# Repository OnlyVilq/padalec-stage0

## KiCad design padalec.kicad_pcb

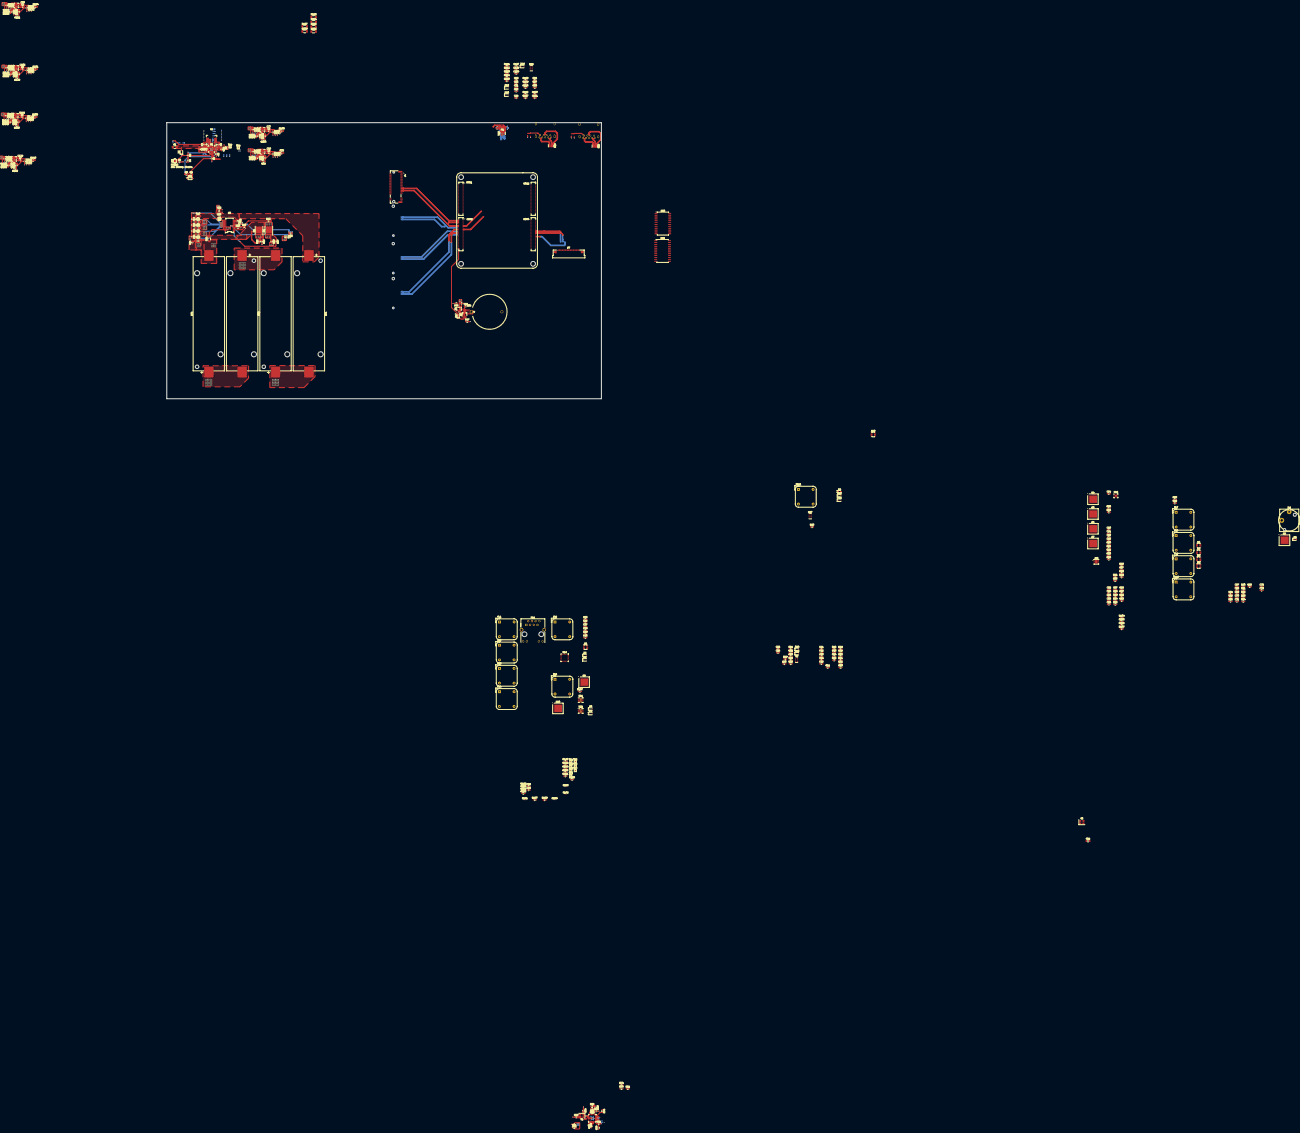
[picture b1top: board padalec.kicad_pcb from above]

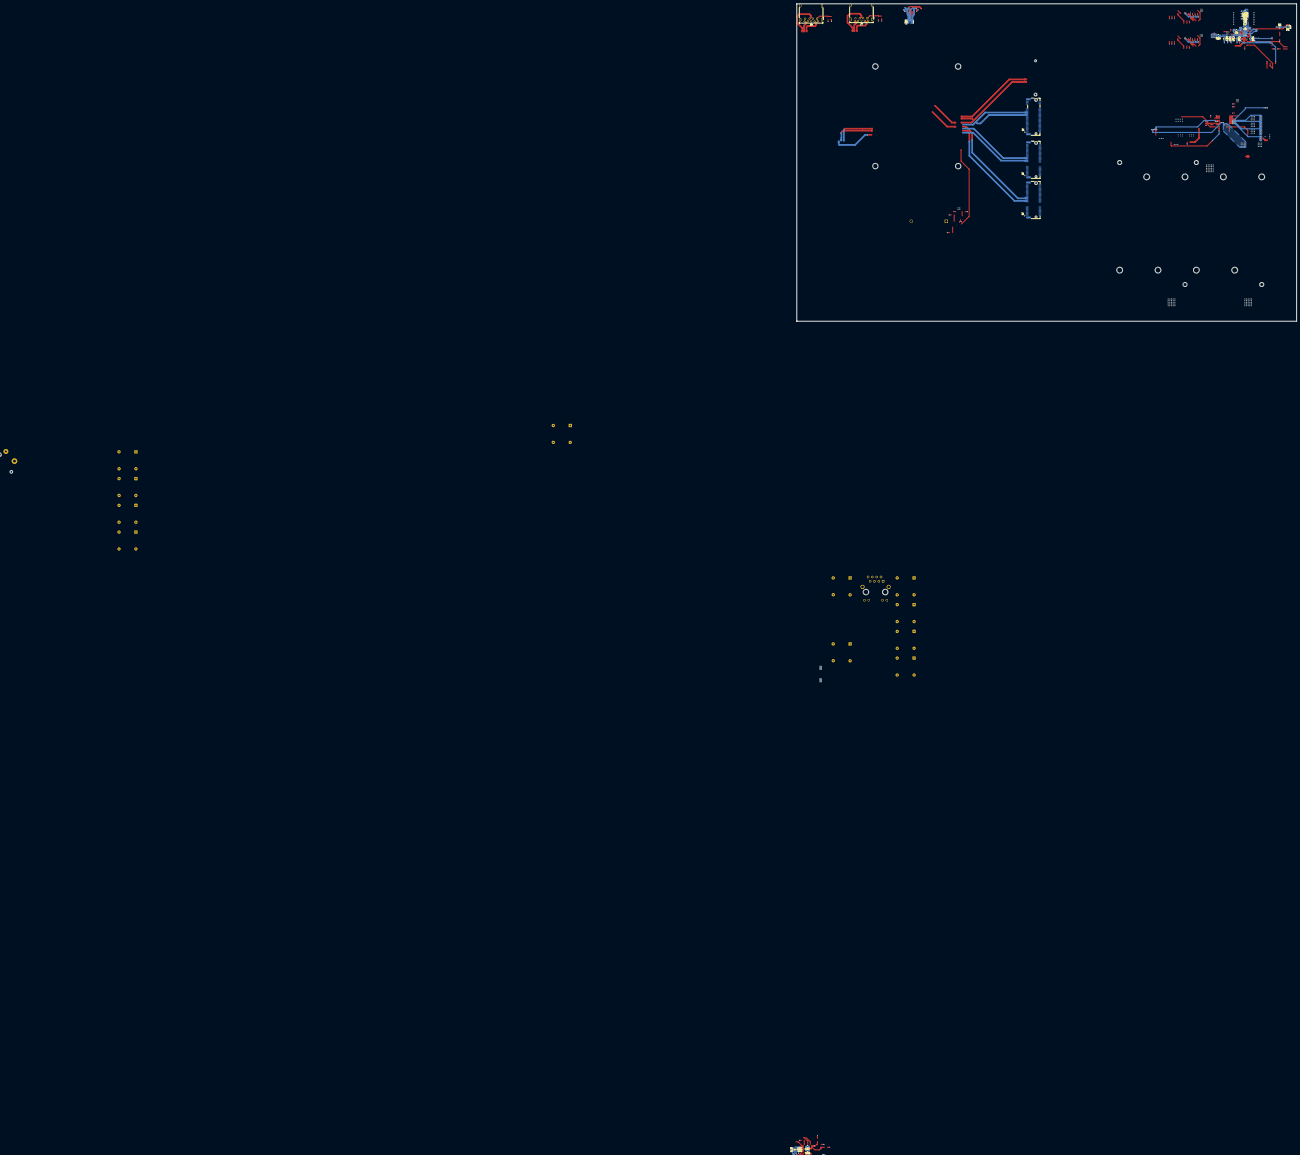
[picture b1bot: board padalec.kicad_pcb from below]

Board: 4 copper layers, 296.0 x 188.0 mm, 408 parts (26 on the bottom side), 299 nets.

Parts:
BT1, BT2, BT3, BT4: Battery_Cell; BatteryHolder_Keystone_1042_1x18650
BT5: Battery_Cell; BatteryHolder_MYOUNG_BS-07-A1BJ001_CR2032
C1, C2, C7, C8, C11, C13, C15, C22, C23, C25, C46, C47, C55, C65, C74, C75, C87, C91, C95, C96, C103, C104, C111, C112, C119, C120: 10u; C_0603_1608Metric_Pad1.08x0.95mm_HandSolder
C3, C6, C44, C45, C49, C53, C77, C81, C82, C85, C86, C88, C92, C98, C102, C106, C110, C114, C118, C122, C126: 0.1u; C_0603_1608Metric_Pad1.08x0.95mm_HandSolder
C4, C5: 47n; C_0603_1608Metric_Pad1.08x0.95mm_HandSolder
C9, C33: 1n; C_0603_1608Metric_Pad1.08x0.95mm_HandSolder
C10, C27, C28, C40, C42, C43: 4.7u; C_0603_1608Metric_Pad1.08x0.95mm_HandSolder
C12, C14, C17, C18, C19, C20, C21, C29, C54, C56, C64, C66, C128: 1u; C_0603_1608Metric_Pad1.08x0.95mm_HandSolder
C16, C26, C32, C34, C35, C36, C37, C41, C48, C57, C60, C61, C62, C63, C67, C70, C71, C72, C73, C76, C97, C105, C113, C121, C127, C129, C130, C131: 100n; C_0603_1608Metric_Pad1.08x0.95mm_HandSolder
C24: 10n; C_0603_1608Metric_Pad1.08x0.95mm_HandSolder
C30: 22n; C_0603_1608Metric_Pad1.08x0.95mm_HandSolder
C31: 2.2n; C_0603_1608Metric_Pad1.08x0.95mm_HandSolder
C38, C39: 6p; C_0603_1608Metric_Pad1.08x0.95mm_HandSolder
C50, C99, C107, C115, C123: 2.2u; C_0603_1608Metric_Pad1.08x0.95mm_HandSolder
C51, C52, C79, C80, C100, C101, C108, C109, C116, C117, C124, C125: 22u; C_0603_1608Metric_Pad1.08x0.95mm_HandSolder
C58, C59, C68, C69: 6.8p; C_0603_1608Metric_Pad1.08x0.95mm_HandSolder
C78: 3.3u; C_0603_1608Metric_Pad1.08x0.95mm_HandSolder
C83, C84: 220p; C_0603_1608Metric_Pad1.08x0.95mm_HandSolder
C89, C90, C93, C94: 150u; C_0603_1608Metric_Pad1.08x0.95mm_HandSolder
C132, C133: 33u; C_0603_1608Metric_Pad1.08x0.95mm_HandSolder
D1, D8, D9: LED; LED_0603_1608Metric_Pad1.05x0.95mm_HandSolder
D2, D3, D4, D5, D6, D10, D11, D12, D13, D14, D15, D16: PESD5V0X1BL; D_SOD-323
D7: eDP_30pin; Amphenol_F32Q-1A7x1-11029_1x29-1MP_P0.5mm_Horizontal
D17: BAT54; D_0603_1608Metric_Pad1.05x0.95mm_HandSolder
F1: Fuse; Fuse_1206_3216Metric_Pad1.42x1.75mm_HandSolder
FB1, FB2: BLM21A601R; L_0805_2012Metric_Pad1.05x1.20mm_HandSolder
FL1, FL2, FL3, FL4: Choke_Schaffner_RN102-04-14.0x14.0mm
FL5, FL6, FL7, FL8, FL9, FL10, FL11: DNP; Choke_Schaffner_RN102-04-14.0x14.0mm
J1: CM3588 Hirose Connector; CM3588
J4: Bus_M.2_Socket_M; AMPHENOL_MDT420M03001
J5: Bus_M.2_Socket_M; AMPHENOL_MDT420E03001
J6: Bus_M.2_Socket_E; AMPHENOL_MDT420M03001
J7, J8: USB3_A; USB3_A_Molex_48393-001
J9: Bus_M.2_Socket_E; AMPHENOL_MDT420E03001
J10: HDMI_A; WDFN-10-1EP_3x3mm_P0.5mm_EP1.8x2.5mm
J11: AudioJack3_SwitchTR; Jack_6.35mm_Neutrik_NJ2FD-V_Vertical
JP1: SCRAM; SolderJumper-2_P1.3mm_Open_RoundedPad1.0x1.5mm
L1: SPM6530T-1R0M120; SPM6530
L2, L4, L5, L6, L7: 2.2u; L_0603_1608Metric_Pad1.05x0.95mm_HandSolder
L3: 3.3u; L_0603_1608Metric_Pad1.05x0.95mm_HandSolder
P1: USB_C_Plug; USB_C_Plug_Molex_105444
Q1, Q2: CSD18534Q5A; VSONP-8-1EP_5x6_P1.27mm
Q3: AO3401A; TSOT-23_HandSoldering
Q4: AO3401A; Nordic_AQFN-94-1EP_7x7mm_P0.4mm
Q5: 2N7002; Nordic_AQFN-94-1EP_7x7mm_P0.4mm
Q6, Q7, Q8, Q9, Q10: NMOS; Nordic_AQFN-94-1EP_7x7mm_P0.4mm
R1, R5, R11, R13, R15, R16, R50, R59, R60, R61, R62, R66, R68, R71, R74, R75, R76, R77, R78, R79, R80, R81, R82, R84, R85, R86, R87, R88, R89, R90, R91, R92, R95, R96, R97, R99, R102, R116, R117, R118, R120, R123, R125, R127, R130, R132, R134, R137, R139, R141, R144, R155, R157, R158: 10k; R_0603_1608Metric_Pad0.98x0.95mm_HandSolder
R2, R7: 27k; R_0603_1608Metric_Pad0.98x0.95mm_HandSolder
R3, R54: 0; R_0603_1608Metric_Pad0.98x0.95mm_HandSolder
R4, R30, R36, R37, R38, R39, R40: DNP; R_0603_1608Metric_Pad0.98x0.95mm_HandSolder
R6, R154: 2.2k; R_0603_1608Metric_Pad0.98x0.95mm_HandSolder
R8: 5.24; R_0603_1608Metric_Pad0.98x0.95mm_HandSolder
R9: 30.31 k; R_0603_1608Metric_Pad0.98x0.95mm_HandSolder
R10, R29: 100; R_0603_1608Metric_Pad0.98x0.95mm_HandSolder
R12: 470k; R_0603_1608Metric_Pad0.98x0.95mm_HandSolder
R14, R27: 1k; R_0603_1608Metric_Pad0.98x0.95mm_HandSolder
R17, R46, R93, R94: 47k; R_0603_1608Metric_Pad0.98x0.95mm_HandSolder
R18, R72, R103, R124, R131, R138, R145: 0; R_0805_2012Metric_Pad1.20x1.40mm_HandSolder
R19, R20, R21, R22, R23: 68; R_1206_3216Metric_Pad1.30x1.75mm_HandSolder
R24: 1m; R_1206_3216Metric_Pad1.30x1.75mm_HandSolder
R25, R28, R57: 1M; R_0603_1608Metric_Pad0.98x0.95mm_HandSolder
R26: 4k5; R_0603_1608Metric_Pad0.98x0.95mm_HandSolder
R31, R32, R33, R34, R35, R41, R42, R43, R44: 33; R_0603_1608Metric_Pad0.98x0.95mm_HandSolder
R45, R48: R_Small; R_0603_1608Metric_Pad0.98x0.95mm_HandSolder
R47, R49, R58, R63, R64, R65, R67, R98, R106, R107, R109, R110, R111, R112, R114, R115, R119, R126, R133, R140, R156: 100k; R_0603_1608Metric_Pad0.98x0.95mm_HandSolder
R51: dnp; R_0603_1608Metric_Pad0.98x0.95mm_HandSolder
R52: 10; R_0603_1608Metric_Pad0.98x0.95mm_HandSolder
R53: 4.7k; R_0603_1608Metric_Pad0.98x0.95mm_HandSolder
R55: 10K; R_0603_1608Metric_Pad0.98x0.95mm_HandSolder
R56: 12K; R_0603_1608Metric_Pad0.98x0.95mm_HandSolder
R69, R100, R121, R128, R135, R142: 20k; R_0603_1608Metric_Pad0.98x0.95mm_HandSolder
R70, R122, R129, R136, R143: 45.3k; R_0603_1608Metric_Pad0.98x0.95mm_HandSolder
R73, R83: 1; R_0603_1608Metric_Pad0.98x0.95mm_HandSolder
R101: 73.2k; R_0603_1608Metric_Pad0.98x0.95mm_HandSolder
R104, R105: 2.2K; R_0603_1608Metric_Pad0.98x0.95mm_HandSolder
R108, R113: 37.4k; R_0603_1608Metric_Pad0.98x0.95mm_HandSolder
R146, R147, R148, R149, R150, R151, R152, R153: 499; R_0603_1608Metric_Pad0.98x0.95mm_HandSolder
R159, R160, R161, R162: 10k; R_0201_0603Metric_Pad0.64x0.40mm_HandSolder
R163, R164, R165, R166, R167, R168: 0; R_1206_3216Metric_Pad1.30x1.75mm_HandSolder
TH1, TH2: 103AT Thermistor; PinHeader_2x01_P1.00mm_Vertical_SMD
TP1: PowerEN; TestPoint_Pad_1.0x1.0mm
TP2: +5V; TestPoint_Pad_1.0x1.0mm
TP3: +3V3; TestPoint_Pad_1.0x1.0mm
TP4: 3V3_PCIE_A; TestPoint_Pad_1.0x1.0mm
TP5: 3V3_PCIE_B; TestPoint_Pad_1.0x1.0mm
TP6: 3V3 PCIE_C; TestPoint_Pad_1.0x1.0mm
TP7: 3V3 PCIE_D; TestPoint_Pad_1.0x1.0mm
TP8: VBUS; TestPoint_Pad_1.0x1.0mm
TP9: BAT; TestPoint_Pad_1.0x1.0mm
U1: BQ25798; Texas_RQM0029A_VQFN-29_4x4mm_P0.4mm
U2: BQ7791500PWR; BQ77915
U3, U17, U18, U19, U20, U27, U28: TPD6E05U06RVZ; Texas_R-PUSON-N14
U4: MCP73831-2-OT; SOT-23-5
U5: TPS22810DBV; SOT-23-6
U6: USB2534-1080AEN; SOT-23-6
U7, U8, U9, U10: 82400102; SOT-23-6
U11: TMJUTVW0021192448; RJ45_Hanrun_HR911105A_Horizontal
U12, U15, U23, U24, U25, U26: TPS56637; CONV_TPS56637RPAR
U13, U14: 9FGV0441; UQFN-32_5x5mm_P0.5mm
U16: FUSB302BMPX; WQFN-14-1EP_2.5x2.5mm_P0.5mm_EP1.45x1.45mm
U21, U22: TPS2561; VSON-10-1EP_3x3mm_P0.5mm_EP1.65x2.4mm_ThermalVias
U29, U30: PCA9539xD; SOIC-24W_7.5x15.4mm_P1.27mm
Y2, Y3: FC3BS; Crystal_SMD_3225-4Pin_3.2x2.5mm

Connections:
+1V8: FB1.1, FB2.1, R30.1, R154.1, R156.1
+3V3: C29.1, C130.1, C131.1, R7.1, R45.1, R54.1, R72.2, R104.1, R105.1, R159.1, R160.1, R161.1, R162.1, TP3.1 (1_1), U5.1 (VIN), U11.11, U16.3 (VDD), U16.4 (VDD), U30.24 (V_{DD})
+5V: C27.1, C87.1, C88.1, C91.1, C92.1, R103.2, R109.1, R110.1, R114.1, R115.1, TP2.1 (1_1), U4.4 (V_{DD}), U16.12 (VCONN), U16.13 (VCONN), U21.2 (IN), U21.3 (IN), U22.2 (IN), U22.3 (IN)
/Debug UART/RX: D6.2 (A2), R44.2, R45.2
/Debug UART/TX: D5.2 (A2), R43.2
/Debug UART/UART2_RX: J1.22, R44.1
/Debug UART/UART2_TX: J1.20, R43.1
/EDP 1/Bl_VCC: C30.2, D7.26 (Bl_VCC), D7.27 (Bl_VCC), D7.28 (Bl_VCC), D7.29 (Bl_VCC), R50.2
/EDP 1/LCD_VCC: C32.1, D7.12 (LCD_VCC), D7.13 (LCD_VCC), R51.2, R52.1, U5.6 (VOUT)
/EDP 1/eDP.AUX_N: D7.10 (AUX_N), J1.359
/EDP 1/eDP.AUX_P: D7.9 (AUX_P), J1.357
/EDP 1/eDP.Bl_PWR_EN: R48.1, U30.11 (IO0_7)
/EDP 1/eDP.Logic_EN: U5.3 (EN/UVLO), U30.10 (IO0_6)
/EDP 1/eDP.TX0_N: D7.6 (TX0_N), J1.347
/EDP 1/eDP.TX0_P: D7.7 (TX0_P), J1.345
/EDP 1/eDP.TX1_N: D7.3 (TX1_N), J1.341
/EDP 1/eDP.TX1_P: D7.4 (TX1_P), J1.339
/Ethernet/Gled: C44.1, J1.72, U11.12
/Ethernet/TD1_N: J1.80, U7.3
/Ethernet/TD1_P: J1.78, U7.1
/Ethernet/TD2_N: J1.86, U8.3
/Ethernet/TD2_P: J1.84, U8.1
/Ethernet/TD3_N: J1.92, U9.3
/Ethernet/TD3_P: J1.90, U9.1
/Ethernet/TD4_N: J1.98, U10.3
/Ethernet/TD4_P: J1.96, U10.1
/Ethernet/U10_4: FL1.3, U7.4
/Ethernet/U10_6: FL1.1, U7.6
/Ethernet/U11_4: FL2.3, FL3.3, U8.4
/Ethernet/U11_6: FL2.1, FL3.1, U8.6
/Ethernet/U12_4: FL4.3, U9.4
/Ethernet/U12_6: FL4.1, U9.6
/Ethernet/Yled: C45.1, J1.74
/GPIO expander/PCIEP.3V3_A: R163.1, U30.13 (IO1_0)
/GPIO expander/PCIEP.3V3_B: R164.1, U30.14 (IO1_1)
/GPIO expander/PCIEP.3V3_C: R165.1, U30.15 (IO1_2)
/GPIO expander/PCIEP.3V3_D: R166.1, U30.16 (IO1_3)
/GPIO expander/PCIEP.pGood_A: R119.2, U23.4 (PG), U30.17 (IO1_4)
/GPIO expander/PCIEP.pGood_B: R126.2, U24.4 (PG), U30.18 (IO1_5)
/GPIO expander/PCIEP.pGood_C: R133.2, U25.4 (PG), U30.19 (IO1_6)
/GPIO expander/PCIEP.pGood_D: R140.2, U26.4 (PG), U30.20 (IO1_7)
/GPIO expander/PCIe.~Disable1: J6.56 (~W_DISABLE1), R95.2, U29.4 (IO0_0)
/GPIO expander/PCIe.~Disable2: J6.54 (~W_DISABLE2), R96.2, U29.5 (IO0_1)
/GPIO expander/PCIe.~Disable3: J9.56 (~W_DISABLE1), R116.2, U29.6 (IO0_2)
/GPIO expander/PCIe.~Disable4: J9.54 (~W_DISABLE2), R117.2, U29.7 (IO0_3)
/GPIO expander/USB.EN1: J1.239, R106.1, U21.4 (EN1)
/GPIO expander/USB.EN2: J1.261, R111.1, U22.4 (EN1)
/GPIO expander/USB.EN3: J1.397, R112.1, U22.5 (EN2)
/GPIO expander/USB.~Fault1: R109.2, U21.10 (~FAULT1), U30.5 (IO0_1)
/GPIO expander/USB.~Fault2: R114.2, U22.10 (~FAULT1), U30.6 (IO0_2)
/GPIO expander/USB.~Fault3: R115.2, U22.6 (~FAULT2), U30.7 (IO0_3)
/GPIO expander/expander.SCL: J1.32, R160.2, U30.23 (SDA)
/GPIO expander/expander.SDA: J1.31, R159.2, U30.22 (SCL)
/GPIO expander/expander.~INT: J1.398, R161.2, U30.1 (~INT)
/GPIO expander/~RESET: R162.2, U30.3 (~RESET)
/HDMI_tx/D0+: FL10.2, J10.7 (D0+), U27.9 (D3+)
/HDMI_tx/D0-: FL10.4, J10.9 (D0-), U27.8 (D3-)
/HDMI_tx/D1+: FL9.2, J10.4 (D1+), U27.12 (D2+)
/HDMI_tx/D1-: FL9.4, J10.6 (D1-), U27.11 (D2-)
/HDMI_tx/D2+: FL8.2, J10.1 (D2+), U27.14 (D1+)
/HDMI_tx/D2-: FL8.4, J10.3 (D2-), U27.13 (D1-)
/HDMI_tx/HDMI.D0_N: FL10.3, R148.1
/HDMI_tx/HDMI.D0_P: FL10.1, R149.1
/HDMI_tx/HDMI.D1_N: FL9.3, R150.1
/HDMI_tx/HDMI.D1_P: FL9.1, R151.1
/HDMI_tx/HDMI.D2_N: FL8.3, R152.1
/HDMI_tx/HDMI.D2_P: FL8.1, R153.1
/HDMI_tx/HDMI.D3_N: FL11.3, R146.1
/HDMI_tx/HDMI.D3_P: FL11.1, R147.1
/Jack_35/DET: R156.2, R157.1
/Jack_35/HPL: C127.1, D16.2 (A2), J1.104, J11.T, R155.1
/Jack_35/HPR: C129.1, D15.2 (A2), J1.103, R158.1
/Jack_35/HP_DET: J1.108, R154.2
/PCIE/M2_E_x1/3v3: J6.2 (3.3V), J6.4 (3.3V), J6.72 (3.3V), J6.74 (3.3V), R95.1, R96.1, R138.2, TP6.1 (1_1)
/PCIE/M2_E_x2/3v3: J9.2 (3.3V), J9.4 (3.3V), J9.72 (3.3V), J9.74 (3.3V), R116.1, R117.1, R145.2, TP7.1 (1_1)
/PCIE/M2_M_x1/3v3: J4.2 (3.3V), J4.4 (3.3V), J4.12 (3.3V), J4.14 (3.3V), J4.16 (3.3V), J4.18 (3.3V), J4.70 (3.3V), J4.72 (3.3V), J4.74 (3.3V), R93.1, R124.2, TP4.1 (1_1)
/PCIE/M2_M_x2/3v3: J5.2 (3.3V), J5.4 (3.3V), J5.12 (3.3V), J5.14 (3.3V), J5.16 (3.3V), J5.18 (3.3V), J5.70 (3.3V), J5.72 (3.3V), J5.74 (3.3V), R94.1, R131.2, TP5.1 (1_1)
/PCIE/PCIE CLOCK 0/CK_REF_FG: R75.2, R81.1
/PCIE/PCIE CLOCK 0/FG_OE_0: R77.2, U13.12 (~OE0)
/PCIE/PCIE CLOCK 0/FG_OE_1: R78.2, U13.17 (~OE1)
/PCIE/PCIE CLOCK 0/FG_OE_2: R79.2, U13.24 (~OE2)
/PCIE/PCIE CLOCK 0/FG_OE_3: R80.2, U13.29 (~OE3)
/PCIE/PCIE CLOCK 0/FG_SSEN: R76.2, R82.1, U13.32 (VSS_EN_TRI)
/PCIE/PCIE CLOCK 0/V1P8FG: C55.1, C57.1, C60.1, C61.1, C62.1, C63.1, FB1.2, R73.1, U13.4 (VDDXTAL), U13.5 (VDDREF), U13.9 (VDDDIG), U13.16 (VDDO), U13.25 (VDDO)
/PCIE/PCIE CLOCK 0/V1P8FGA: C54.1, C56.1, R73.2, U13.21 (VDDA)
/PCIE/PCIE CLOCK 0/VCC1P8: R74.1, R75.1, R76.1
/PCIE/PCIE CLOCK 1/CK_REF_FG: R85.2, R91.1
/PCIE/PCIE CLOCK 1/FG_OE_0: R87.2, U14.12 (~OE0)
/PCIE/PCIE CLOCK 1/FG_OE_1: R88.2, U14.17 (~OE1)
/PCIE/PCIE CLOCK 1/FG_OE_2: R89.2, U14.24 (~OE2)
/PCIE/PCIE CLOCK 1/FG_OE_3: R90.2, U14.29 (~OE3)
/PCIE/PCIE CLOCK 1/FG_SSEN: R86.2, R92.1, U14.32 (VSS_EN_TRI)
/PCIE/PCIE CLOCK 1/V1P8FG: C65.1, C67.1, C70.1, C71.1, C72.1, C73.1, FB2.2, R83.1, U14.4 (VDDXTAL), U14.5 (VDDREF), U14.9 (VDDDIG), U14.16 (VDDO), U14.25 (VDDO)
/PCIE/PCIE CLOCK 1/V1P8FGA: C64.1, C66.1, R83.2, U14.21 (VDDA)
/PCIE/PCIE CLOCK 1/VCC1P8: R84.1, R85.1, R86.1
/PCIE/Port_1.REFCLK_N: J1.260, U14.14 (~DIF0)
/PCIE/Port_1.REFCLK_P: J1.258, U14.13 (DIF0)
/RK3588/Charger.PowerEN: J1.19, R167.1, TP1.1 (1_1)
/RK3588/Charger.SCL: J1.28, U1.14 (SCL)
/RK3588/Charger.SDA: J1.30, U1.15 (SDA)
/RK3588/Charger.~INT: R7.2, U1.21 (~INT)
/RK3588/PWRON: C24.1, J1.17, R29.2
/RK3588/PortA.RXN: J1.206, J4.43 (PERp0/SATA-B-)
/RK3588/PortA.RXP: J1.204, J4.41 (PERn0/SATA-B+)
/RK3588/PortA.TXN: J1.224, J4.49 (PETp0/SATA-A+)
/RK3588/PortA.TXP: J1.222, J4.47 (PETn0/SATA-A-)
/RK3588/PortB.RXN: J1.212, J5.43 (PERp0/SATA-B-)
/RK3588/PortB.RXP: J1.210, J5.41 (PERn0/SATA-B+)
/RK3588/PortB.TXN: J1.230, J5.49 (PETp0/SATA-A+)
/RK3588/PortB.TXP: J1.228, J5.47 (PETn0/SATA-A-)
/RK3588/PortC.RXN: J1.236, J6.43 (PERn0)
/RK3588/PortC.RXP: J1.234, J6.41 (PERp0)
/RK3588/PortC.TXN: J1.248, J6.37 (PETn0)
/RK3588/PortC.TXP: J1.246, J6.35 (PETp0)
/RK3588/PortD.RXN: J1.242, J9.43 (PERn0)
/RK3588/PortD.RXP: J1.240, J9.41 (PERp0)
/RK3588/PortD.TXN: J1.254, J9.37 (PETn0)
/RK3588/PortD.TXP: J1.252, J9.35 (PETp0)
/RK3588/RTC_bat: D17.2 (A), J1.300
/RK3588/SD_0.CLK: J1.360, R41.1, R41.2, U3.11 (D2-)
/RK3588/SD_0.CMD: J1.356, R35.1, R35.2, R40.2, U3.12 (D2+)
/RK3588/SD_0.D0: J1.364, R31.1
/RK3588/SD_0.D1: J1.366, R32.1
/RK3588/SD_0.D2: J1.352, R33.1
/RK3588/SD_0.D3: J1.354, R34.1
/RK3588/SD_0.DET: J1.370, R30.2, R42.2
/RK3588/SD_0.VDD: C25.1, C26.1, D4.2 (A2), J1.358, R36.1, R37.1, R38.1, R39.1, R40.1
/RK3588/USB3_host_0.D_N: J7.2 (D-), U19.14 (D1+)
/RK3588/USB3_host_0.D_P: J7.3 (D+), U19.13 (D1-)
/RK3588/USB3_host_0.SSRX_N: J1.223, J7.5 (SSRX-), U19.12 (D2+)
/RK3588/USB3_host_0.SSRX_P: J1.221, J7.6 (SSRX+), U19.11 (D2-)
/RK3588/USB3_host_0.SSTX_N: J1.235, J7.8 (SSTX-), U19.9 (D3+)
/RK3588/USB3_host_0.SSTX_P: J1.233, J7.9 (SSTX+), U19.8 (D3-)
/RK3588/USB3_host_1.D_N: J1.198, J8.2 (D-), U20.14 (D1+)
/RK3588/USB3_host_1.D_P: J1.196, J8.3 (D+), U20.13 (D1-)
/RK3588/USB3_host_1.SSRX_N: J1.197, J8.5 (SSRX-), U20.12 (D2+)
/RK3588/USB3_host_1.SSRX_P: J1.195, J8.6 (SSRX+), U20.11 (D2-)
/RK3588/USB3_host_1.SSTX_N: J1.191, J8.8 (SSTX-), U20.9 (D3+)
/RK3588/USB3_host_1.SSTX_P: J1.189, J8.9 (SSTX+), U20.8 (D3-)
/RK3588/USBC_host_0.D_N: J1.192, P1.A7 (D-), U18.11 (D2-)
/RK3588/USBC_host_0.D_P: J1.190, P1.A6 (D+), U18.12 (D2+)
/RK3588/USBC_host_0.SBU1: J1.304, P1.A8 (SBU1), U17.12 (D2+)
/RK3588/USBC_host_0.SBU2: J1.306, P1.B8 (SBU2), U17.11 (D2-)
/RK3588/USBC_host_0.SCL: J1.296, R104.2, U16.6 (SCL)
/RK3588/USBC_host_0.SDA: J1.298, R105.2, U16.7 (SDA)
/RK3588/USBC_host_0.SSRX2_N: J1.161, P1.A10 (RX2-), U18.9 (D3+)
/RK3588/USBC_host_0.SSRX2_P: J1.159, P1.A11 (RX2+), U18.8 (D3-)
/RK3588/USBC_host_0.SSRX_N: J1.173, P1.B10 (RX1-), U17.9 (D3+)
/RK3588/USBC_host_0.SSRX_P: J1.171, P1.B11 (RX1+), U17.8 (D3-)
/RK3588/USBC_host_0.SSTX2_N: J1.155, P1.B3 (TX2-), U17.13 (D1-)
/RK3588/USBC_host_0.SSTX2_P: J1.153, P1.B2 (TX2+), U17.14 (D1+)
/RK3588/USBC_host_0.SSTX_N: J1.167, P1.A3 (TX1-), U18.13 (D1-)
/RK3588/USBC_host_0.SSTX_P: J1.165, P1.A2 (TX1+), U18.14 (D1+)
/RK3588/USBC_host_0.~CC_Int: J1.264, U16.5 (INT_N)
/RTC/+5v: Q3.2 (G), R47.1
/USB-external/5v5_A0: C85.2, C94.1, D13.2 (A2), J7.1 (VBUS), U22.9 (OUT1)
/USB-external/5v5_C0: C82.2, C90.1, D10.2 (A2), P1.A4 (VBUS), P1.A9 (VBUS), P1.B4 (VBUS), P1.B9 (VBUS), U16.2 (VBUS), U21.9 (OUT1)
/USB-external/5v5_C1: C86.2, C93.1, D14.2 (A2), J8.1 (VBUS), U22.8 (OUT2)
/USB-external/Power switch/5v5_out_2: C89.1, U21.8 (OUT2)
/USB-external/Power switch/EN2: R107.1, U21.5 (EN2)
/USB-external/Power switch/~FAULT2: R110.2, U21.6 (~FAULT2)
/USB-external/USB 3.x C/CC1: C84.1, D11.2 (A2), P1.A5 (CC), U16.10 (CC1), U16.11 (CC1)
/USB-external/USB 3.x C/CC2: C83.1, D12.2 (A2), P1.B5 (VCONN), U16.1 (CC2), U16.14 (CC2)
/USB-internal/3v3: C34.1, C35.1, C36.1, C37.1, C40.1, C41.1, C42.1, C43.1, R53.1, R54.2, R59.2, R60.2, R61.2, R62.2, R64.1, R65.1
/USB-internal/USB20_hub_DS1.D_N: J6.5 (USB_D-), U6.1 (USBDN1_DM), U6.2 (USBDN1_DP)
/USB-internal/USB20_hub_DS2.D_N: J9.5 (USB_D-), U6.3 (USBDN2_DM), U6.4 (USBDN2_DP)
/USB-internal/vbus_det: C33.1, R53.2
/USB-internal/~RESET: R55.2, U30.4 (IO0_0)
/Zasilanie/3V3/PowerGood: R67.2, U12.4 (PG)
/Zasilanie/3V3/en: R66.1, R168.2, U12.1 (EN)
/Zasilanie/3V3_1/en: R118.1, R163.2, U23.1 (EN)
/Zasilanie/3V3_2/en: R125.1, R164.2, U24.1 (EN)
/Zasilanie/3V3_3/en: R132.1, R165.2, U25.1 (EN)
/Zasilanie/3V3_4/en: R139.1, R166.2, U26.1 (EN)
/Zasilanie/5V/PowerGood: R98.2, R168.1, U15.4 (PG)
/Zasilanie/5V/en: R97.1, R167.2, U15.1 (EN)
/Zasilanie/Bat: BT1.1 (+), C22.1, C23.1, R10.1, R11.1, R14.1, R19.2, TP9.1 (1_1), U1.22 (BAT), U1.23 (BAT)
/Zasilanie/CCFG: C12.1, U2.2 (AVDD), U2.20 (CCFG)
/Zasilanie/CHG: R27.1, U2.13 (CHG)
/Zasilanie/Charging_LED: D1.1 (K), U1.1 (STAT)
/Zasilanie/DSG: R26.1, U2.12 (DSG)
/Zasilanie/ILIM_HIZ: R3.2, R4.1, U1.17 (ILIM_HIZ)
/Zasilanie/PROG: R2.1, U1.20 (PROG)
/Zasilanie/REGN: C10.1, R3.1, R6.1, R8.1, U1.5 (REGN)
/Zasilanie/SRN: Q1.3 (S), R24.2, R25.2, U2.11 (SRN)
/Zasilanie/VC0: C21.2, R23.1, U2.8 (VC0)
/Zasilanie/VC1: C19.2, C20.1, R22.1, U2.7 (VC1)
/Zasilanie/VC2: C18.2, C19.1, R21.1, U2.6 (VC2)
/Zasilanie/VC3: C17.2, C18.1, R20.1, U2.5 (VC3)
/Zasilanie/VC4: C17.1, R19.1, U2.3 (VC5), U2.4 (VC4)
/Zasilanie/vsys: C13.1, C15.1, C16.1, R17.1, R18.1, U1.25 (SYS)
/Zasilanie/~CE: R1.1, U1.13 (~CE)
/Zasilanie/~QON: JP1.2 (B), U1.12 (~QON)
/microSD/DAT0: R31.2, R36.2, U3.9 (D3+)
/microSD/DAT1: R32.2, R37.2, U3.8 (D3-)
/microSD/DAT2: R33.2, R38.2, U3.14 (D1+)
/microSD/DAT3: R34.2, R39.2, U3.13 (D1-)
/microSD/DET_A: D3.2 (A2), R42.1
AGND: R71.2, R102.2, R123.2, R130.2, R137.2, R144.2, U12.3 (AGnd), U15.3 (AGnd), U23.3 (AGnd), U24.3 (AGnd), U25.3 (AGnd), U26.3 (AGnd)
BGND: BT4.2 (-), C20.2, C21.1, R23.2, R24.1, U2.9 (VSS), U2.10 (SRP)
GND: BT5.2 (-), C1.2, C2.2, C3.2, C6.2, C7.2, C8.2, C9.2, C10.2, C11.2, C12.2, C13.2, C14.2, C15.2, C16.2, C22.2, C23.2, C24.2, C25.2, C26.2, C27.2, C28.2, C29.2, C31.2, C32.2, C33.2, C34.2, C35.2, C36.2, C37.2, C38.1, C39.1, C40.2, C41.2, C42.2, C43.2, C44.2, C45.2, C46.2, C47.2, C48.2, C51.2, C52.2, C53.2, C54.2, C55.2, C56.2, C57.2, C58.1, C59.1, C60.2, C61.2, C62.2, C63.2, C64.2, C65.2, C66.2, C67.2, C68.1, C69.1, C70.2, C71.2, C72.2, C73.2, C74.2, C75.2, C76.2, C79.2, C80.2, C81.2, C82.1, C83.2, C84.2, C85.1, C86.1, C87.2, C88.2, C89.2, C90.2, C91.2, C92.2, C93.2, C94.2, C95.2, C96.2, C97.2, C100.2, C101.2, C102.2, C103.2, C104.2, C105.2, C108.2, C109.2, C110.2, C111.2, C112.2, C113.2, C116.2, C117.2, C118.2, C119.2, C120.2, C121.2, C124.2, C125.2, C126.2, C128.2, C130.2, C131.2, C132.2, C133.2, D2.1 (A1), D3.1 (A1), D4.1 (A1), D5.1 (A1), D6.1 (A1), D7.2 (Hs_GND), D7.5 (Hs_GND), D7.8 (Hs_GND), D7.11 (Hs_GND), D7.15 (Hs_GND), D7.16 (Hs_GND), D7.18 (Bl_GND), D7.19 (Bl_GND), D7.20 (Bl_GND), D7.21 (Bl_GND), D10.1 (A1), D11.1 (A1), D12.1 (A1), D13.1 (A1), D14.1 (A1), D15.1 (A1), D16.1 (A1), J1.11, J1.12, J1.13, J1.24, J1.33, J1.34, J1.39, J1.40, J1.45, J1.46, J1.51, J1.52, J1.57, J1.58, J1.63, J1.64, J1.69, J1.70, J1.73, J1.76, J1.77, J1.82, J1.88, J1.91, J1.94, J1.100, J1.121, J1.127, J1.133, J1.139, J1.145, J1.151, J1.157, J1.163, J1.169, J1.175, J1.181, J1.187, J1.193, J1.199, J1.201, J1.207, J1.213, J1.219, J1.225, J1.231, J1.237, J1.331, J1.337, J1.343, J1.349, J1.355, J1.361, J4.1 (GND), J4.3 (GND), J4.9 (GND), J4.15 (GND), J4.21 (GND), J4.27 (GND), J4.33 (GND), J4.39 (GND), J4.45 (GND), J4.51 (GND), J4.57 (GND), J4.71 (GND), J4.73 (GND), J4.75 (GND), J5.1 (GND), J5.3 (GND), J5.9 (GND), J5.15 (GND), J5.21 (GND), J5.33 (GND), J5.39 (GND), J5.45 (GND), J5.51 (GND), J5.57 (GND), J5.71 (GND), J5.73 (GND), J5.75 (GND), J6.1 (GND), J6.7 (GND), J6.18 (GND), J6.33 (GND), J6.39 (GND), J6.45 (GND), J6.51 (GND), J6.57 (GND), J6.69 (GND), J6.75 (GND), J7.4 (GND), J7.7 (DRAIN), J7.SH (SHIELD), J8.4 (GND), J8.7 (DRAIN), J8.SH (SHIELD), J9.1 (GND), J9.7 (GND), J9.18 (GND), J9.33 (GND), J9.39 (GND), J9.45 (GND), J9.51 (GND), J9.57 (GND), J9.63 (GND), J9.69 (GND), J9.75 (GND), P1.A1 (GND), P1.A12 (GND), P1.B1 (GND), P1.B12 (GND), P1.SH (SHIELD), Q2.3 (S), R1.2, R2.2, R4.2, R5.2, R9.2, R12.2, R13.2, R16.2, R17.2, R28.2, R46.2, R47.2, R52.2, R55.1, R56.1, R58.2, R63.2, R66.2, R68.2, R77.1, R78.1, R79.1, R80.1, R81.2, R82.2, R87.1, R88.1, R89.1, R90.1, R91.2, R92.2, R97.2, R99.2, R106.2, R107.2, R108.2, R111.2, R112.2, R113.2, R118.2, R120.2, R125.2, R127.2, R132.2, R134.2, R139.2, R141.2, TH1.2, TH2.2, U1.10 (ACDRV2), U1.11 (ACDRV1), U1.27 (GND), U2.23 (CTRC), U2.24 (CTRD), U3.5 (GND), U3.10 (GND), U4.2 (V_{SS}), U5.2 (GND), U7.2, U8.2, U9.2, U10.2, U12.9 (PGnd), U13.1 (GNDXTAL), U13.7 (GNDREF), U13.8 (GNDDIG), U13.15 (GND), U13.20 (GNDA), U13.26 (GND), U13.30 (GND), U14.1 (GNDXTAL), U14.7 (GNDREF), U14.8 (GNDDIG), U14.15 (GND), U14.20 (GNDA), U14.26 (GND), U14.30 (GND), U15.9 (PGnd), U16.8 (GND), U16.9 (GND), U16.15 (GND), U17.5 (GND), U17.10 (GND), U18.5 (GND), U18.10 (GND), U19.5 (GND), U19.10 (GND), U20.5 (GND), U20.10 (GND), U21.1 (GND), U21.11 (PAD), U22.1 (GND), U22.11 (PAD), U23.9 (PGnd), U24.9 (PGnd), U25.9 (PGnd), U26.9 (PGnd), U27.5 (GND), U27.10 (GND), U30.2 (A1), U30.12 (V_{SS}), U30.21 (A0), Y2.2 (G), Y2.4 (G), Y3.2 (G), Y3.4 (G)
GNDA: C127.2, C129.2, J1.102, J11.S, R155.2, R158.2
unnamed: BT1.2 (-), BT2.1 (+), R20.2
unnamed: BT2.2 (-), BT3.1 (+), R21.2
unnamed: BT3.2 (-), BT4.1 (+), R22.2
unnamed: BT5.1 (+), C28.1, Q3.3 (S), U4.3 (V_{BAT})
unnamed: C50.1, R69.2
unnamed: C51.1, C52.1, C53.1, L2.2, R69.1, R70.1, R72.1
unnamed: C78.1, R100.2
unnamed: C79.1, C80.1, C81.1, L3.2, R100.1, R101.1, R103.1
unnamed: C99.1, R121.2
unnamed: C100.1, C101.1, C102.1, L4.2, R121.1, R122.1, R124.1
unnamed: C107.1, R128.2
unnamed: C108.1, C109.1, C110.1, L5.2, R128.1, R129.1, R131.1
unnamed: C115.1, R135.2
unnamed: C116.1, C117.1, C118.1, L6.2, R135.1, R136.1, R138.1
unnamed: C123.1, R142.2
unnamed: C124.1, C125.1, C126.1, L7.2, R142.1, R143.1, R145.1
unnamed: D1.2 (A), R6.2
unnamed: C1.1, C2.1, C3.1, D2.2 (A2), F1.2, U1.2 (VBUS), U1.3 (VBUS), U1.8 (VAC2), U1.9 (VAC1)
unnamed: D8.2 (A), R93.2
unnamed: D8.1 (K), J4.10 (DAS/~DSS/~LED1)
unnamed: D9.2 (A), R94.2
unnamed: D9.1 (K), J5.10 (DAS/~DSS/~LED1)
unnamed: D17.1 (K), Q3.1 (D)
unnamed: J1.302, J1.308, J1.314
unnamed: J1.350, J1.362, J1.368
unnamed: JP1.1 (A), R5.1
unnamed: Q1.1 (D), Q2.1 (D)
unnamed: Q1.2 (G), R25.1, R26.2
unnamed: Q2.2 (G), R27.2, R28.1
unnamed: C30.1, R49.2, R50.1
unnamed: R146.2, R147.2
unnamed: R148.2, R149.2
unnamed: R150.2, R151.2
unnamed: R152.2, R153.2
unnamed: C128.1, R157.2
unnamed: R10.2, U1.18 (BATP)
unnamed: C4.1, U1.4 (BTST1)
unnamed: C5.2, U1.19 (BTST2)
unnamed: C6.1, C7.1, C8.1, C11.1, C132.1, C133.1, U1.29 (PMID)
unnamed: C9.1, U1.24 (SDRV)
unnamed: C4.2, L1.1, U1.28 (SW1)
unnamed: C5.1, L1.2, U1.26 (SW2)
unnamed: R8.2, R9.1, TH1.1, U1.16 (TS)
unnamed: R16.1, U2.16 (CBI)
unnamed: R12.1, U2.14 (LD)
unnamed: R13.1, U2.17 (OCDP)
unnamed: R11.2, U2.22 (PRES)
unnamed: R15.2, TH2.1, U2.18 (TS)
unnamed: C14.1, R14.2, U2.1 (VDD)
unnamed: R15.1, U2.19 (VTB)
unnamed: R46.1, U4.5 (PROG)
unnamed: C31.1, U5.4 (CT)
unnamed: R51.1, U5.5 (QOD)
unnamed: C38.2, R57.1
unnamed: C39.2, R57.2
unnamed: FL1.2, U11.1 (TD1+)
unnamed: FL1.4, U11.2 (TD1-)
unnamed: FL2.2, U11.3 (TD2+)
unnamed: FL2.4, U11.4 (TD2-)
unnamed: FL3.2, U11.7 (TD3+)
unnamed: FL3.4, U11.8 (TD3-)
unnamed: FL4.2, U11.9 (TD4+)
unnamed: FL4.4, U11.10 (TD4-)
unnamed: C49.1, U12.7 (Boot)
unnamed: C50.2, R70.2, R71.1, U12.2 (FB)
unnamed: R68.1, U12.10 (Mode)
unnamed: C49.2, L2.1, U12.6 (SW)
unnamed: C59.2, U13.3 (X2), Y2.3
unnamed: C58.2, U13.2 (XIN/CLKIN_25), Y2.1
unnamed: C69.2, U14.3 (X2), Y3.3
unnamed: C68.2, U14.2 (XIN/CLKIN_25), Y3.1
unnamed: C77.1, U15.7 (Boot)
unnamed: C78.2, R101.2, R102.1, U15.2 (FB)
unnamed: R99.1, U15.10 (Mode)
unnamed: C77.2, L3.1, U15.6 (SW)
unnamed: R108.1, U21.7 (ILM)
unnamed: R113.1, U22.7 (ILM)
unnamed: C98.1, U23.7 (Boot)
unnamed: C99.2, R122.2, R123.1, U23.2 (FB)
unnamed: R120.1, U23.10 (Mode)
unnamed: C98.2, L4.1, U23.6 (SW)
unnamed: C106.1, U24.7 (Boot)
unnamed: C107.2, R129.2, R130.1, U24.2 (FB)
unnamed: R127.1, U24.10 (Mode)
unnamed: C106.2, L5.1, U24.6 (SW)
unnamed: C114.1, U25.7 (Boot)
unnamed: C115.2, R136.2, R137.1, U25.2 (FB)
unnamed: R134.1, U25.10 (Mode)
unnamed: C114.2, L6.1, U25.6 (SW)
unnamed: C122.1, U26.7 (Boot)
unnamed: C123.2, R143.2, R144.1, U26.2 (FB)
unnamed: R141.1, U26.10 (Mode)
unnamed: C122.2, L7.1, U26.6 (SW)
unnamed: FL11.2, U28.14 (D1+)
unnamed: FL11.4, U28.13 (D1-)
unnamed: U28.5 (GND), U28.10 (GND)
VBUS: C46.1, C47.1, C48.1, C74.1, C75.1, C76.1, C95.1, C96.1, C97.1, C103.1, C104.1, C105.1, C111.1, C112.1, C113.1, C119.1, C120.1, C121.1, J1.1, J1.2, J1.3, J1.4, J1.5, J1.6, J1.7, J1.8, J1.9, J1.10, R18.2, R49.1, R67.1, R98.1, R119.1, R126.1, R133.1, R140.1, TP8.1 (1_1), U7.5, U8.5, U9.5, U10.5, U12.8 (Vin), U15.8 (Vin), U23.8 (Vin), U24.8 (Vin), U25.8 (Vin), U26.8 (Vin)
